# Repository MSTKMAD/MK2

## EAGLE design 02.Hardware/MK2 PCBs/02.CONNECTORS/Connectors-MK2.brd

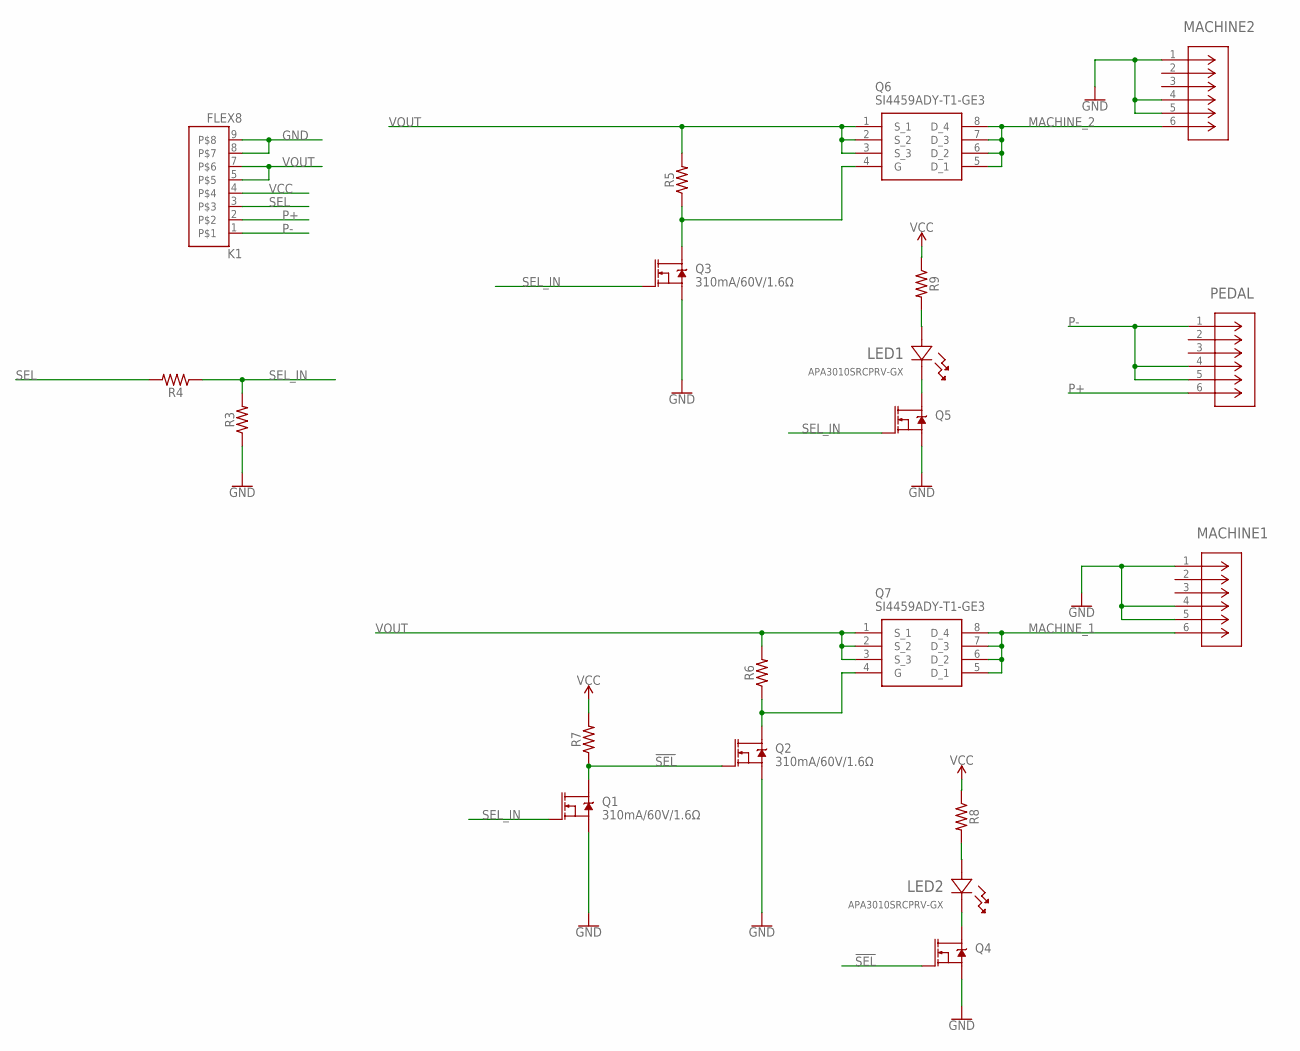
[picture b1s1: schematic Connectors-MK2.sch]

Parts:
K1: FLEX8
LED1, LED2: APA3010SRCPRV-GX; LED_APA3010SRCPRV-GX_KNB
MACHINE1, MACHINE2: ACJS-MHDR; CONN_MHDR_AMP
PEDAL: ACJS-MHDR; CONN_MHDR_AMP
Q1, Q2, Q3, Q4, Q5: 310mA/60V/1.6Ω; SOT323
Q6, Q7: SI4459ADY-T1-GE3; SOIC127P600X175-8N
R3, R4, R5, R6, R7: 0603
R8, R9: 0805

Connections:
!SEL!: Q1.3 (D), Q2.1 (G), Q4.1 (G), R7.1
GND: K1.8, K1.9, MACHINE1.1, MACHINE1.4, MACHINE1.5, MACHINE2.1, MACHINE2.4, MACHINE2.5, Q1.2 (S), Q2.2 (S), Q3.2 (S), Q4.2 (S), Q5.2 (S), R3.1
MACHINE_1: MACHINE1.6, Q7.5 (D_1), Q7.6 (D_2), Q7.7 (D_3), Q7.8 (D_4)
MACHINE_2: MACHINE2.6, Q6.5 (D_1), Q6.6 (D_2), Q6.7 (D_3), Q6.8 (D_4)
unnamed: Q2.3 (D), Q7.4 (G), R6.1
unnamed: Q3.3 (D), Q6.4 (G), R5.1
unnamed: LED2.2, R8.2
unnamed: LED2.1, Q4.3 (D)
unnamed: LED1.2, R9.2
unnamed: LED1.1, Q5.3 (D)
P+: K1.2, PEDAL.6
P-: K1.1, PEDAL.1, PEDAL.4, PEDAL.5
SEL: K1.3, R4.2
SEL_IN: Q1.1 (G), Q3.1 (G), Q5.1 (G), R3.2, R4.1
VCC: K1.4, R7.2, R8.1, R9.1
VOUT: K1.5, K1.7, Q6.1 (S_1), Q6.2 (S_2), Q6.3 (S_3), Q7.1 (S_1), Q7.2 (S_2), Q7.3 (S_3), R5.2, R6.2

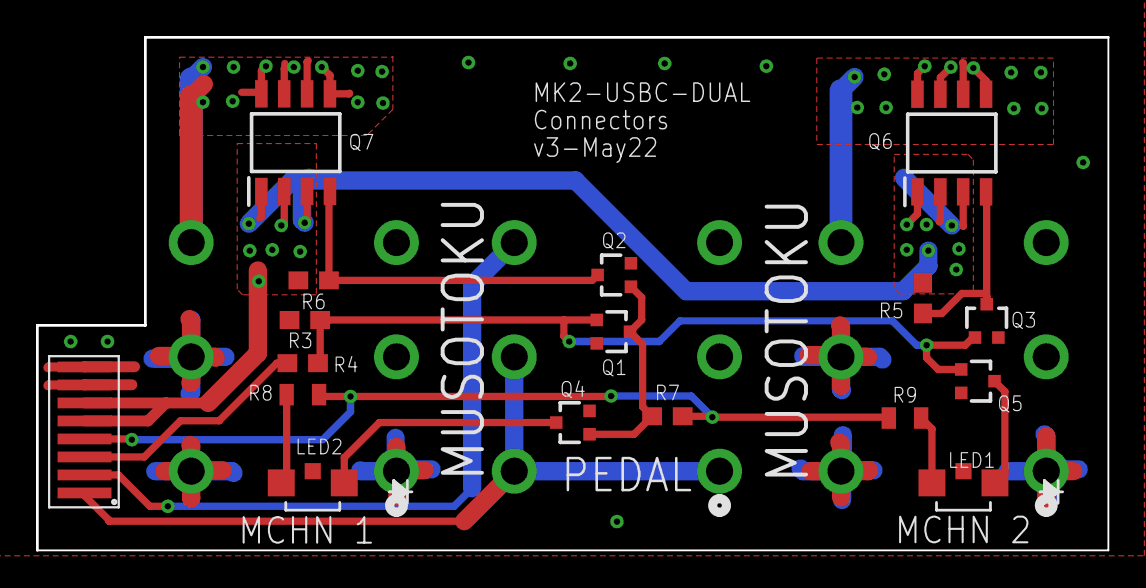
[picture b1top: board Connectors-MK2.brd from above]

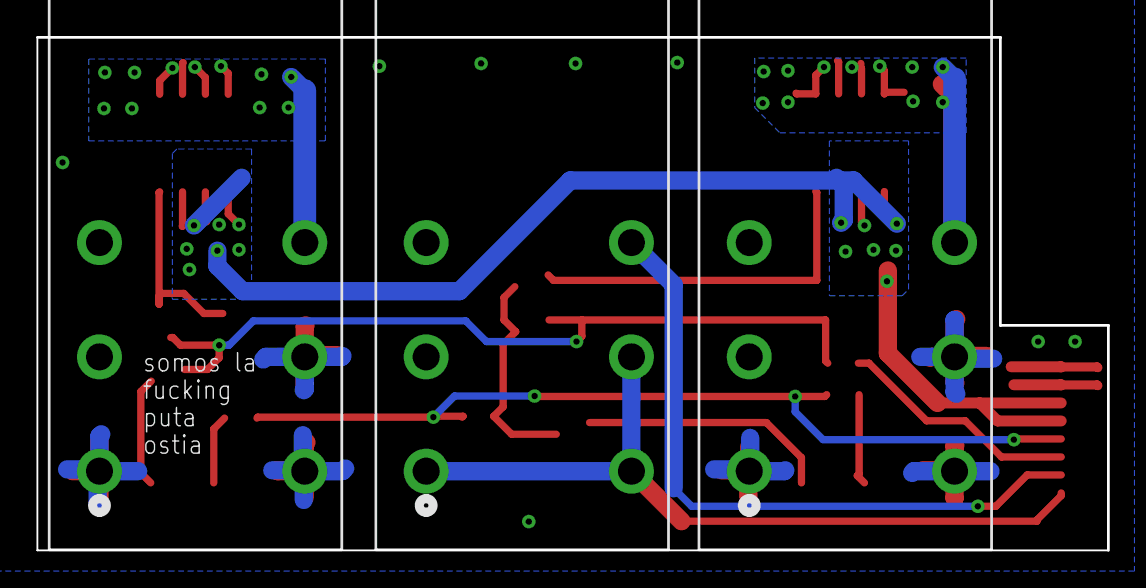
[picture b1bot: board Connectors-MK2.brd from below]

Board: 2 copper layers, 59.5 x 28.5 mm, 20 parts (3 on the bottom side), 16 nets.

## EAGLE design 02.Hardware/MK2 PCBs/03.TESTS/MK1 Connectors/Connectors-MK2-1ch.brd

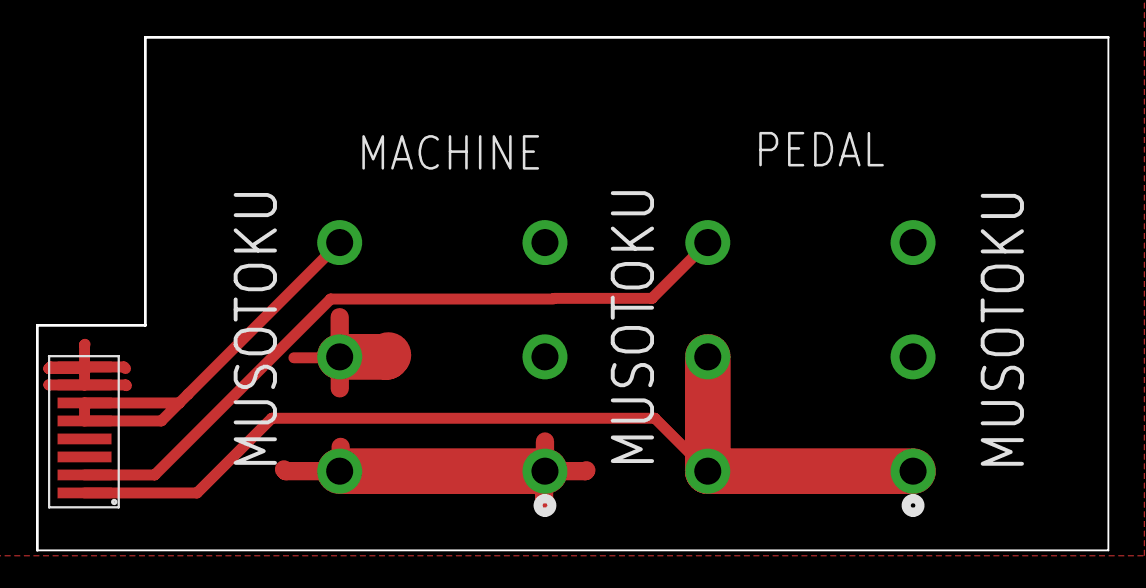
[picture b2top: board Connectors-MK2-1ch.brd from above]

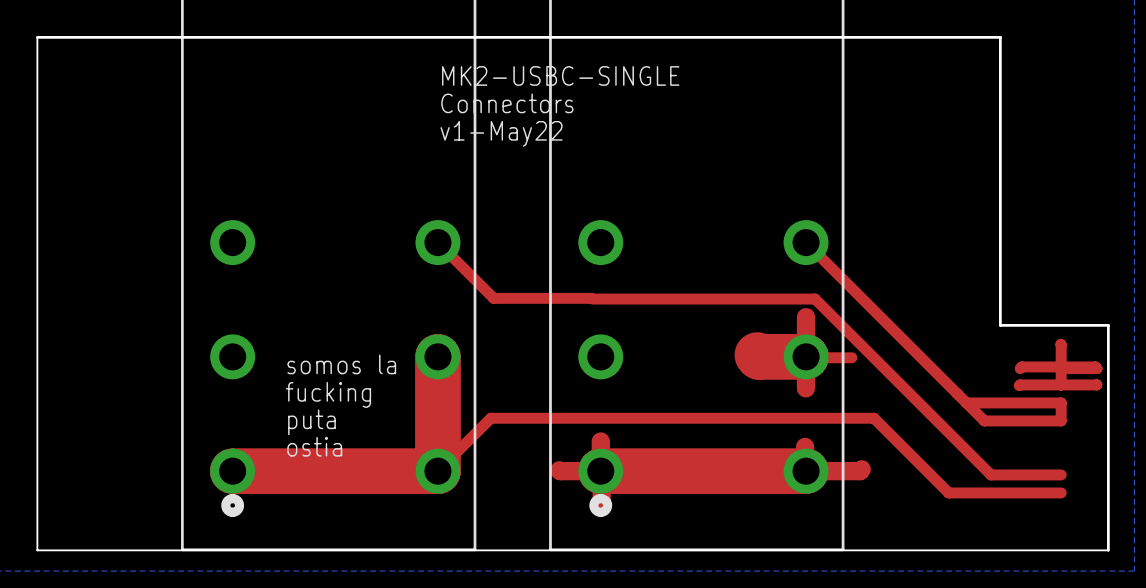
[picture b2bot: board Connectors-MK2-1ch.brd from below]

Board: 2 copper layers, 59.5 x 28.5 mm, 3 parts (2 on the bottom side), 4 nets.

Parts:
K1: FLEX8
MACHINE3, MACHINE4: ACJS-MHDR; CONN_MHDR_AMP

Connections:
GND: K1.8, K1.9, MACHINE3.1, MACHINE3.4, MACHINE3.5
P+: K1.2, MACHINE4.6
P-: K1.1, MACHINE4.1, MACHINE4.4, MACHINE4.5
VOUT: K1.5, K1.7, MACHINE3.6

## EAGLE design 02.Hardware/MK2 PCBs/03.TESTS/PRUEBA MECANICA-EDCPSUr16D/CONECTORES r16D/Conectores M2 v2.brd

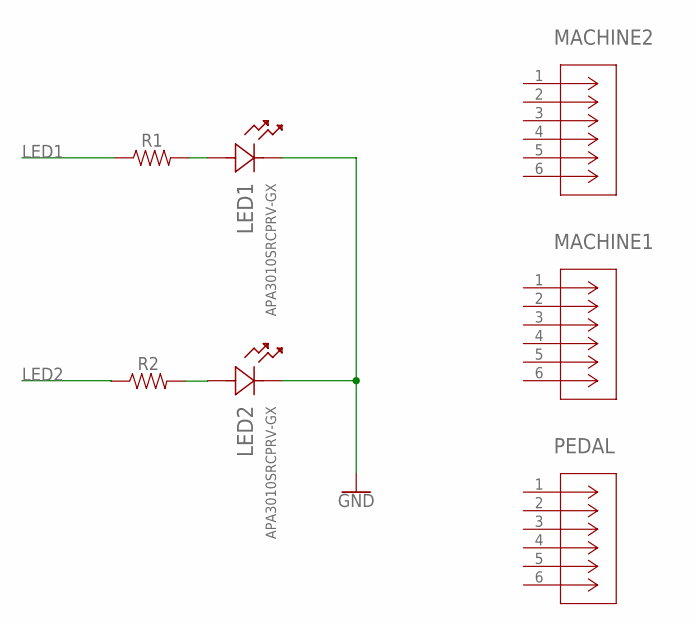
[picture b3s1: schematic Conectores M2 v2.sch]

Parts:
LED1, LED2: APA3010SRCPRV-GX; LED_APA3010SRCPRV-GX_KNB
MACHINE1, MACHINE2: ACJS-MHDR; CONN_MHDR_AMP
PEDAL: ACJS-MHDR; CONN_MHDR_AMP
R1, R2: 0805

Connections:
GND: LED1.1, LED2.1
LED1: R1.1
LED2: R2.1
unnamed: LED2.2, R2.2
unnamed: LED1.2, R1.2

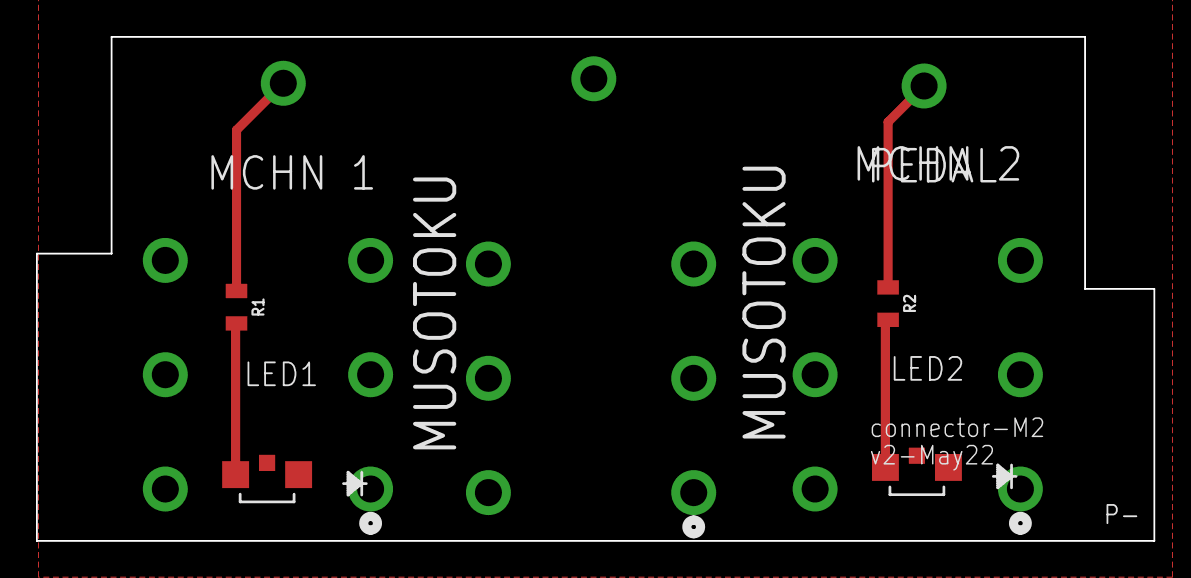
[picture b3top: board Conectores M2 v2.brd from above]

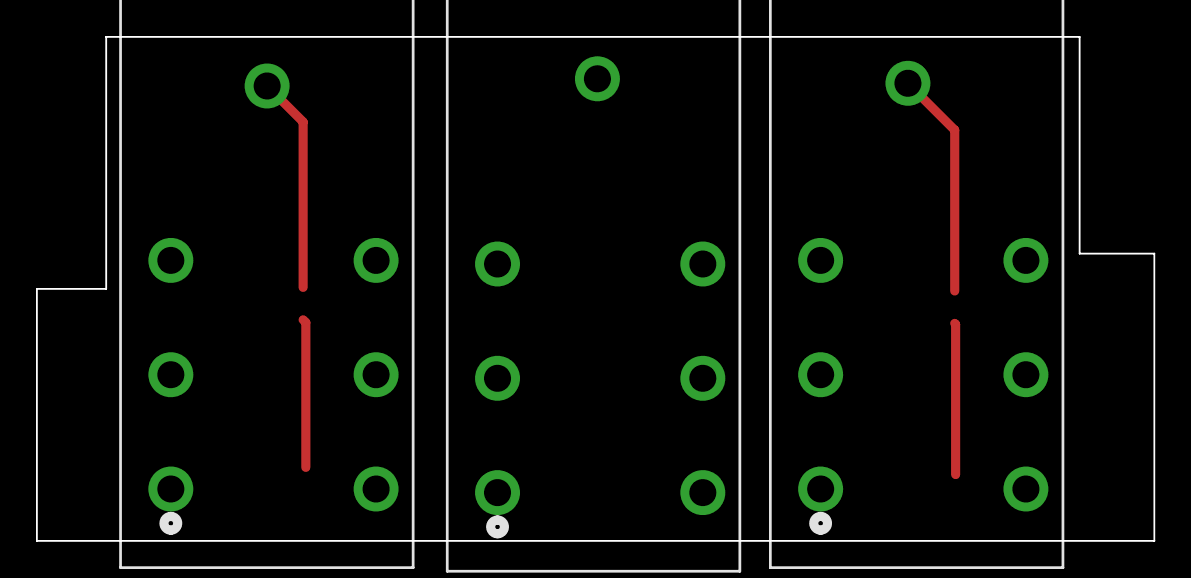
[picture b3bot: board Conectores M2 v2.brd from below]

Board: 2 copper layers, 62.1 x 28.0 mm, 7 parts (3 on the bottom side), 3 nets.

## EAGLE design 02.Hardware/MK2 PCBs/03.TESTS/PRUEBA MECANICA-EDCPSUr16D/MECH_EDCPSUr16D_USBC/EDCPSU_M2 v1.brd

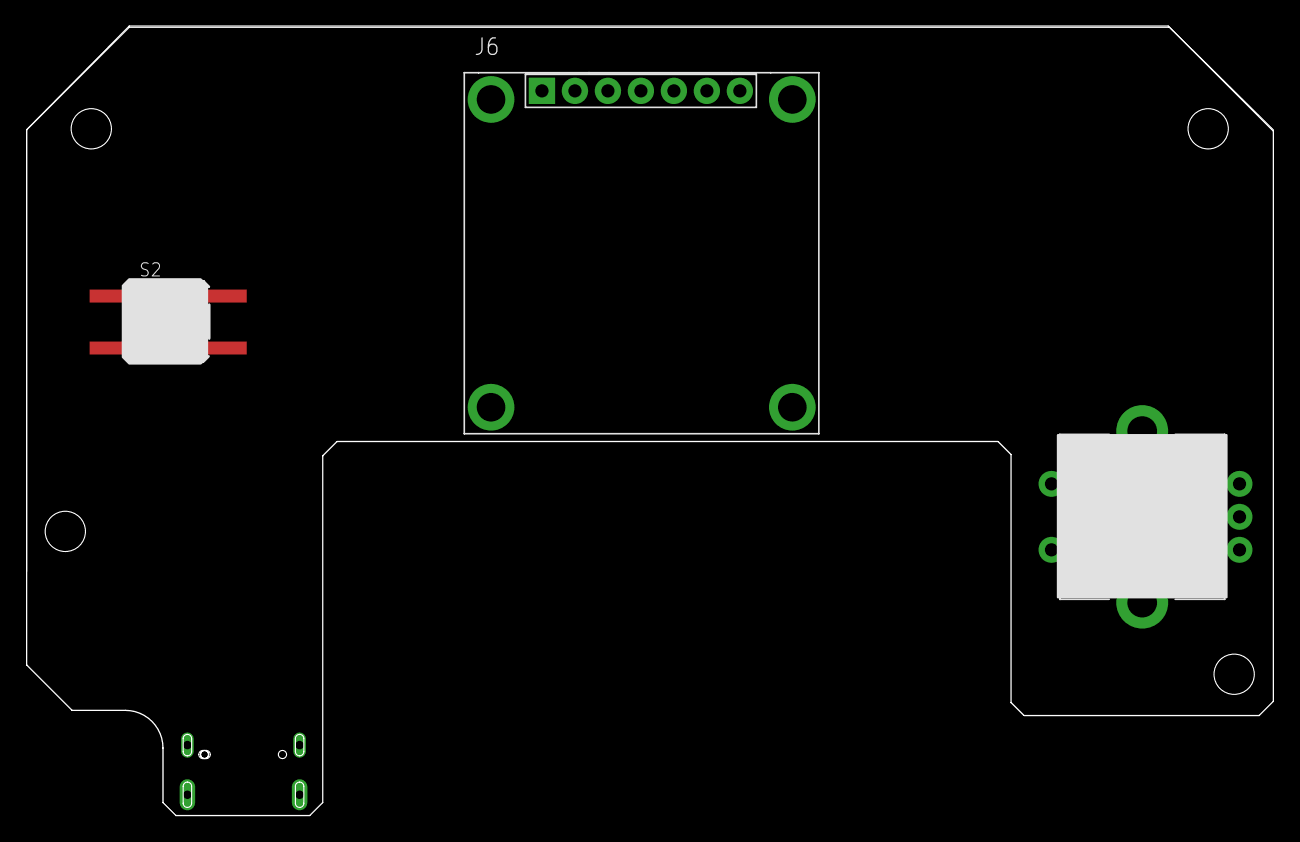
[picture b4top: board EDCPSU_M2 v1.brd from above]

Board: 4 copper layers, 96.0 x 60.7 mm, 4 parts (1 on the bottom side), 2 nets, no tracks yet.

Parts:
J4: DX07S016JA1R1500; JAE_DX07S016JA1R1500
J6: Display; OLED_LCD
S1: ROTARTY_ENCODER; ROTARY_ENC_PLAIN
S2: TAC_SW_SMD_KSC931G

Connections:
GND: J4.1, J4.12
VBUS: J4.2, J4.11

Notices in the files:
parts and their libraries:
SparkFun-Resistors: Licensing: Creative Commons ShareAlike 4.0 International - https://creativecommons.org/licenses/by-sa/4.0
COPYRIGHT: Copyright (C) 2018 Accelerated Designs. All rights reserved
